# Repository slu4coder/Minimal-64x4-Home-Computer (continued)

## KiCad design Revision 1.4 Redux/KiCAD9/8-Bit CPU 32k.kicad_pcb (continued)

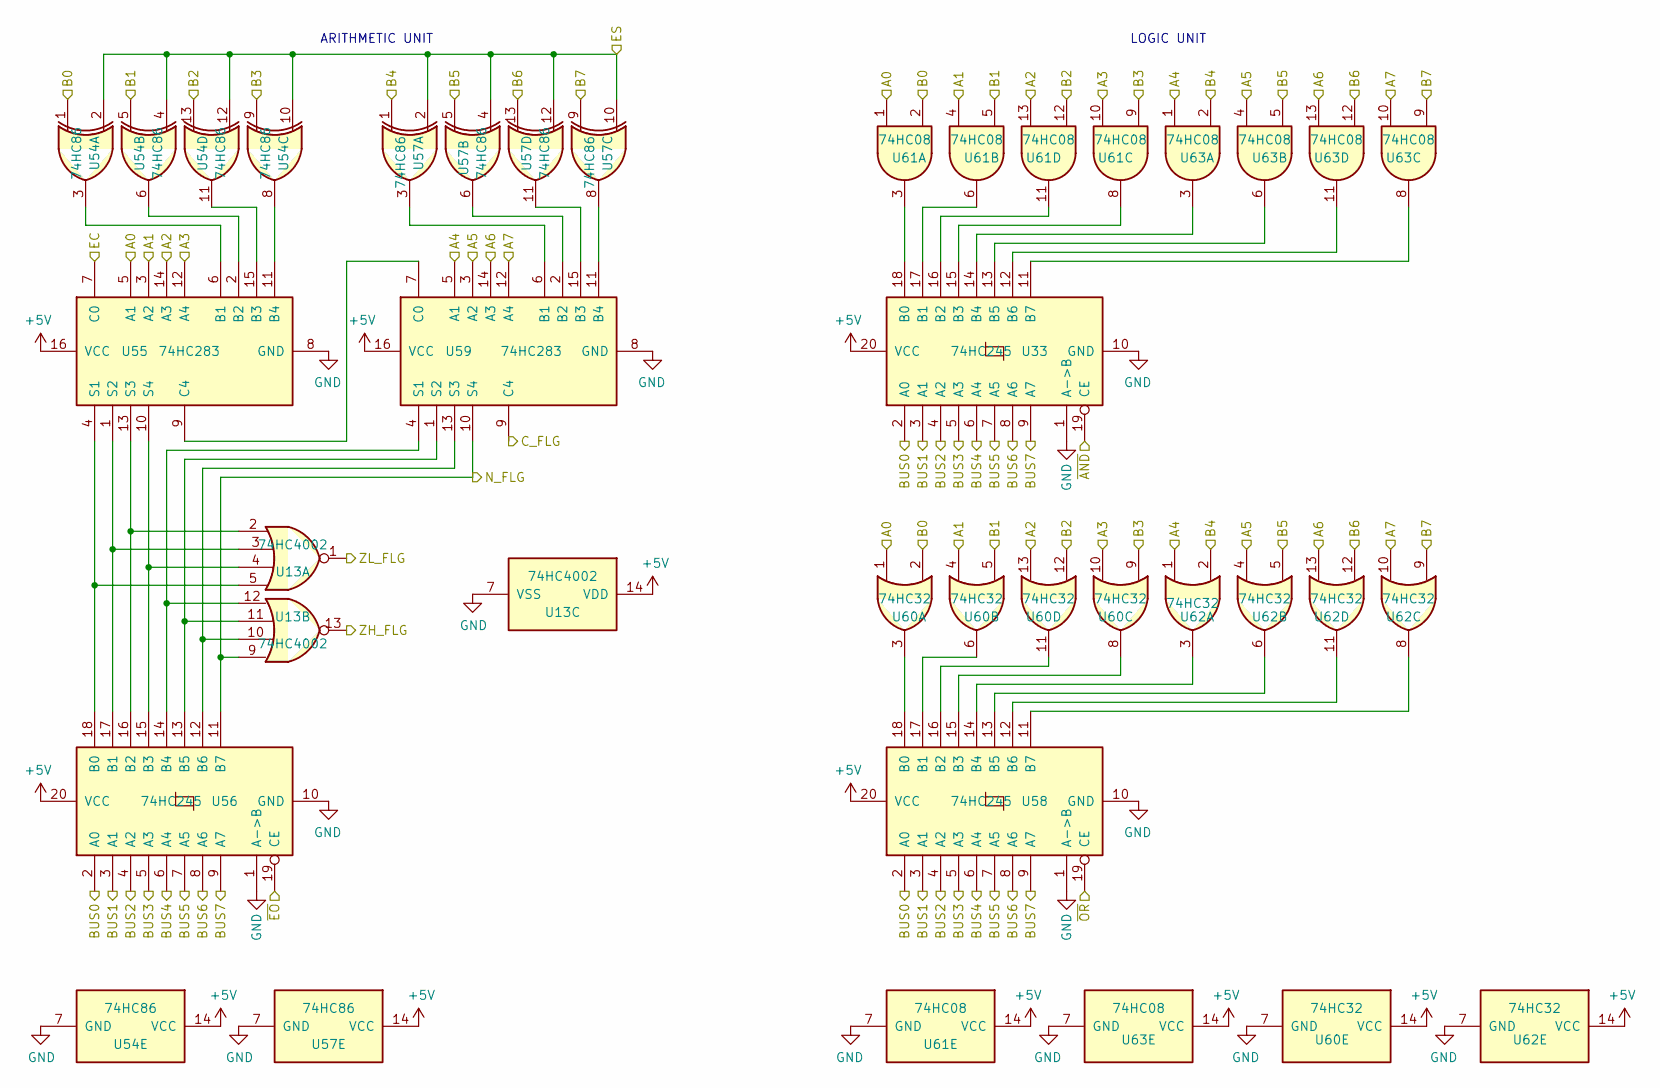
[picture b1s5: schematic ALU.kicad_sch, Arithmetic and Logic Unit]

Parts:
U13: 74HC4002; DIP-14_W7.62mm_Socket
U33, U56, U58: 74HC245; DIP-20_W7.62mm_Socket
U54, U57: 74HC86; DIP-14_W7.62mm_Socket
U55, U59: 74HC283; DIP-16_W7.62mm_Socket
U60, U62: 74HC32; DIP-14_W7.62mm_Socket
U61, U63: 74HC08; DIP-14_W7.62mm_Socket

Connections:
+5V: U13.14 (VDD), U33.20 (VCC), U54.14 (VCC), U55.16 (VCC), U56.20 (VCC), U57.14 (VCC), U58.20 (VCC), U59.16 (VCC), U60.14 (VCC), U61.14 (VCC), U62.14 (VCC), U63.14 (VCC); also elsewhere on the board
/ALU/A0: U55.5 (A1), U60.1, U61.1; also elsewhere on the board
/ALU/A1: U55.3 (A2), U60.4, U61.4; also elsewhere on the board
/ALU/A2: U55.14 (A3), U60.13, U61.13; also elsewhere on the board
/ALU/A3: U55.12 (A4), U60.10, U61.10; also elsewhere on the board
/ALU/A4: U59.5 (A1), U62.1, U63.1; also elsewhere on the board
/ALU/A5: U59.3 (A2), U62.4, U63.4; also elsewhere on the board
/ALU/A6: U59.14 (A3), U62.13, U63.13; also elsewhere on the board
/ALU/A7: U59.12 (A4), U62.10, U63.10; also elsewhere on the board
/ALU/B0: U54.1, U60.2, U61.2; also elsewhere on the board
/ALU/B1: U54.5, U60.5, U61.5; also elsewhere on the board
/ALU/B2: U54.13, U60.12, U61.12; also elsewhere on the board
/ALU/B3: U54.9, U60.9, U61.9; also elsewhere on the board
/ALU/B4: U57.1, U62.2, U63.2; also elsewhere on the board
/ALU/B5: U57.5, U62.5, U63.5; also elsewhere on the board
/ALU/B6: U57.13, U62.12, U63.12; also elsewhere on the board
/ALU/B7: U57.9, U62.9, U63.9; also elsewhere on the board
/ALU/BUS0: U33.2 (A0), U56.2 (A0), U58.2 (A0); also elsewhere on the board
/ALU/BUS1: U33.3 (A1), U56.3 (A1), U58.3 (A1); also elsewhere on the board
/ALU/BUS2: U33.4 (A2), U56.4 (A2), U58.4 (A2); also elsewhere on the board
/ALU/BUS3: U33.5 (A3), U56.5 (A3), U58.5 (A3); also elsewhere on the board
/ALU/BUS4: U33.6 (A4), U56.6 (A4), U58.6 (A4); also elsewhere on the board
/ALU/BUS5: U33.7 (A5), U56.7 (A5), U58.7 (A5); also elsewhere on the board
/ALU/BUS6: U33.8 (A6), U56.8 (A6), U58.8 (A6); also elsewhere on the board
/ALU/BUS7: U33.9 (A7), U56.9 (A7), U58.9 (A7); also elsewhere on the board
/ALU/C_FLG: U59.9 (C4); also elsewhere on the board
/ALU/EC: U55.7 (C0); also elsewhere on the board
/ALU/ES: U54.2, U54.4, U54.10, U54.12, U57.2, U57.4, U57.10, U57.12; also elsewhere on the board
/ALU/N_FLG: U13.9, U56.11 (B7), U59.10 (S4); also elsewhere on the board
/ALU/ZH_FLG: U13.13; also elsewhere on the board
/ALU/ZL_FLG: U13.1; also elsewhere on the board
/ALU/~AND: U33.19 (CE); also elsewhere on the board
/ALU/~EO: U56.19 (CE); also elsewhere on the board
/ALU/~OR: U58.19 (CE); also elsewhere on the board
GND: U13.7 (VSS), U33.1 (A->B), U33.10 (GND), U54.7 (GND), U55.8 (GND), U56.1 (A->B), U56.10 (GND), U57.7 (GND), U58.1 (A->B), U58.10 (GND), U59.8 (GND), U60.7 (GND), U61.7 (GND), U62.7 (GND), U63.7 (GND); also elsewhere on the board
unnamed: U33.18 (B0), U61.3
unnamed: U33.17 (B1), U61.6
unnamed: U33.16 (B2), U61.11
unnamed: U33.15 (B3), U61.8
unnamed: U33.14 (B4), U63.3
unnamed: U33.13 (B5), U63.6
unnamed: U33.12 (B6), U63.11
unnamed: U33.11 (B7), U63.8
unnamed: U54.3, U55.6 (B1)
unnamed: U54.6, U55.2 (B2)
unnamed: U54.11, U55.15 (B3)
unnamed: U54.8, U55.11 (B4)
unnamed: U55.9 (C4), U59.7 (C0)
unnamed: U13.5, U55.4 (S1), U56.18 (B0)
unnamed: U13.3, U55.1 (S2), U56.17 (B1)
unnamed: U13.2, U55.13 (S3), U56.16 (B2)
unnamed: U13.4, U55.10 (S4), U56.15 (B3)
unnamed: U13.12, U56.14 (B4), U59.4 (S1)
unnamed: U13.11, U56.13 (B5), U59.1 (S2)
unnamed: U13.10, U56.12 (B6), U59.13 (S3)
unnamed: U58.18 (B0), U60.3
unnamed: U58.17 (B1), U60.6
unnamed: U58.16 (B2), U60.11
unnamed: U58.15 (B3), U60.8
unnamed: U58.14 (B4), U62.3
unnamed: U58.13 (B5), U62.6
unnamed: U58.12 (B6), U62.11
unnamed: U58.11 (B7), U62.8
unnamed: U57.3, U59.6 (B1)
unnamed: U57.6, U59.2 (B2)
unnamed: U57.11, U59.15 (B3)
unnamed: U57.8, U59.11 (B4)

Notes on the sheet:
ARITHMETIC UNIT
LOGIC UNIT

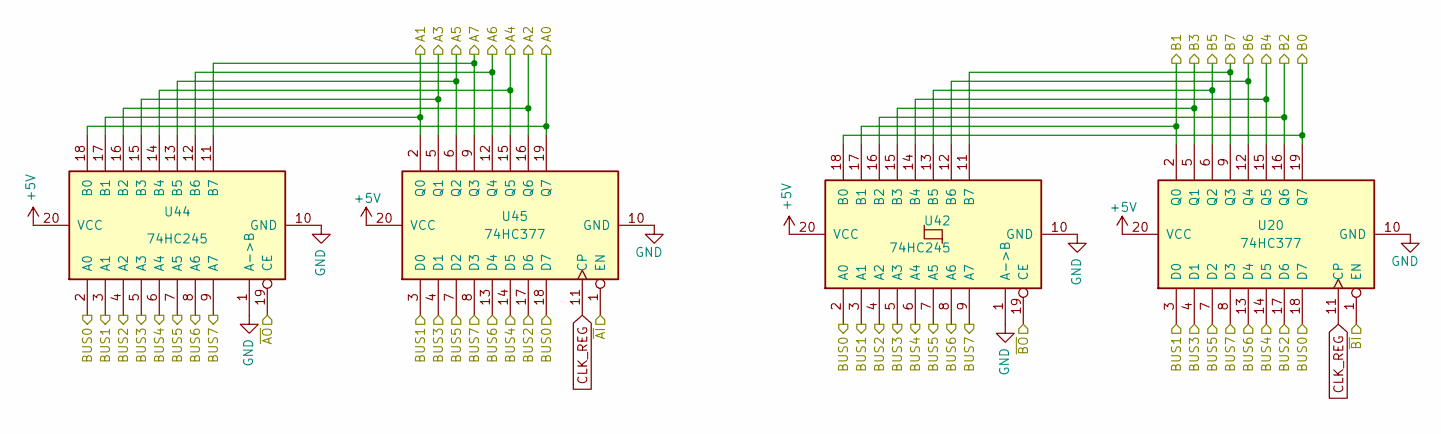
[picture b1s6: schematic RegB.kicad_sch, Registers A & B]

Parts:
U20, U45: 74HC377; DIP-20_W7.62mm_Socket
U42, U44: 74HC245; DIP-20_W7.62mm_Socket

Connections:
+5V: U20.20 (VCC), U42.20 (VCC), U44.20 (VCC), U45.20 (VCC); also elsewhere on the board
/ALU/A0: U44.18 (B0), U45.19 (Q7); also elsewhere on the board
/ALU/A1: U44.17 (B1), U45.2 (Q0); also elsewhere on the board
/ALU/A2: U44.16 (B2), U45.16 (Q6); also elsewhere on the board
/ALU/A3: U44.15 (B3), U45.5 (Q1); also elsewhere on the board
/ALU/A4: U44.14 (B4), U45.15 (Q5); also elsewhere on the board
/ALU/A5: U44.13 (B5), U45.6 (Q2); also elsewhere on the board
/ALU/A6: U44.12 (B6), U45.12 (Q4); also elsewhere on the board
/ALU/A7: U44.11 (B7), U45.9 (Q3); also elsewhere on the board
/ALU/B0: U20.19 (Q7), U42.18 (B0); also elsewhere on the board
/ALU/B1: U20.2 (Q0), U42.17 (B1); also elsewhere on the board
/ALU/B2: U20.16 (Q6), U42.16 (B2); also elsewhere on the board
/ALU/B3: U20.5 (Q1), U42.15 (B3); also elsewhere on the board
/ALU/B4: U20.15 (Q5), U42.14 (B4); also elsewhere on the board
/ALU/B5: U20.6 (Q2), U42.13 (B5); also elsewhere on the board
/ALU/B6: U20.12 (Q4), U42.12 (B6); also elsewhere on the board
/ALU/B7: U20.9 (Q3), U42.11 (B7); also elsewhere on the board
/ALU/BUS0: U20.18 (D7), U42.2 (A0), U44.2 (A0), U45.18 (D7); also elsewhere on the board
/ALU/BUS1: U20.3 (D0), U42.3 (A1), U44.3 (A1), U45.3 (D0); also elsewhere on the board
/ALU/BUS2: U20.17 (D6), U42.4 (A2), U44.4 (A2), U45.17 (D6); also elsewhere on the board
/ALU/BUS3: U20.4 (D1), U42.5 (A3), U44.5 (A3), U45.4 (D1); also elsewhere on the board
/ALU/BUS4: U20.14 (D5), U42.6 (A4), U44.6 (A4), U45.14 (D5); also elsewhere on the board
/ALU/BUS5: U20.7 (D2), U42.7 (A5), U44.7 (A5), U45.7 (D2); also elsewhere on the board
/ALU/BUS6: U20.13 (D4), U42.8 (A6), U44.8 (A6), U45.13 (D4); also elsewhere on the board
/ALU/BUS7: U20.8 (D3), U42.9 (A7), U44.9 (A7), U45.8 (D3); also elsewhere on the board
/Control Logic/~AI: U45.1 (EN); also elsewhere on the board
/Control Logic/~AO: U44.19 (CE); also elsewhere on the board
/Control Logic/~BI: U20.1 (EN); also elsewhere on the board
/Control Logic/~BO: U42.19 (CE); also elsewhere on the board
CLK_REG: U20.11 (CP), U45.11 (CP); also elsewhere on the board
GND: U20.10 (GND), U42.1 (A->B), U42.10 (GND), U44.1 (A->B), U44.10 (GND), U45.10 (GND); also elsewhere on the board

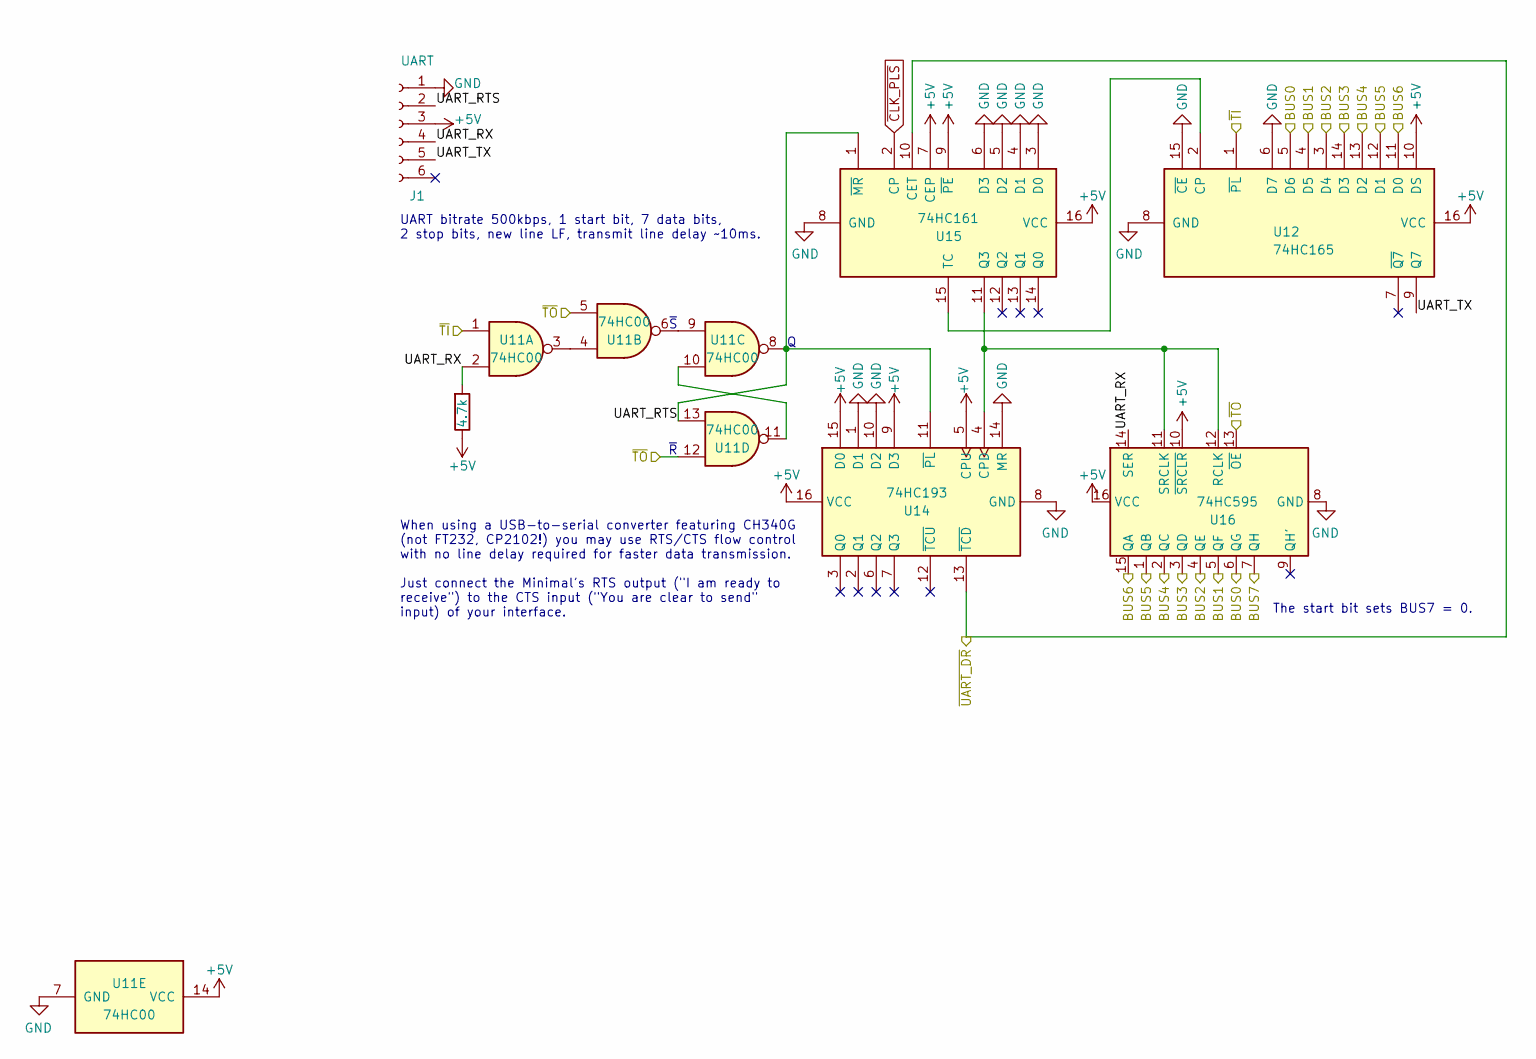
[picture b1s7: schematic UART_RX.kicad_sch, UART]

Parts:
J1: UART; PinSocket_1x06_P2.54mm_Vertical
R1: 4.7k; R_Axial_DIN0207_L6.3mm_D2.5mm_P7.62mm_Horizontal
U11: 74HC00; DIP-14_W7.62mm_Socket
U12: 74HC165; DIP-16_W7.62mm_Socket
U14: 74HC193; DIP-16_W7.62mm_Socket
U15: 74HC161; DIP-16_W7.62mm_Socket
U16: 74HC595; DIP-16_W7.62mm_Socket

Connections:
+5V: J1.3, R1.1, U11.14 (VCC), U12.10 (DS), U12.16 (VCC), U14.5 (CPU), U14.9 (D3), U14.15 (D0), U14.16 (VCC), U15.7 (CEP), U15.9 (~PE), U15.16 (VCC), U16.10 (~SRCLR), U16.16 (VCC); also elsewhere on the board
/ALU/BUS0: U12.5 (D6), U16.6 (QG); also elsewhere on the board
/ALU/BUS1: U12.4 (D5), U16.5 (QF); also elsewhere on the board
/ALU/BUS2: U12.3 (D4), U16.4 (QE); also elsewhere on the board
/ALU/BUS3: U12.14 (D3), U16.3 (QD); also elsewhere on the board
/ALU/BUS4: U12.13 (D2), U16.2 (QC); also elsewhere on the board
/ALU/BUS5: U12.12 (D1), U16.1 (QB); also elsewhere on the board
/ALU/BUS6: U12.11 (D0), U16.15 (QA); also elsewhere on the board
/ALU/BUS7: U16.7 (QH); also elsewhere on the board
/Control Logic/~TI: U11.1, U12.1 (~PL); also elsewhere on the board
/Control Logic/~TO: U11.5, U11.12, U16.13 (~OE); also elsewhere on the board
/Control Logic/~UART_DR: U14.13 (~TCD), U15.10 (CET); also elsewhere on the board
/UART/UART_RTS: J1.2, U11.8, U11.13, U14.11 (~PL), U15.1 (~MR)
/UART/UART_RX: J1.4, R1.2, U11.2, U16.14 (SER)
/UART/UART_TX: J1.5, U12.9 (Q7)
GND: J1.1, U11.7 (GND), U12.6 (D7), U12.8 (GND), U12.15 (~CE), U14.1 (D1), U14.8 (GND), U14.10 (D2), U14.14 (MR), U15.3 (D0), U15.4 (D1), U15.5 (D2), U15.6 (D3), U15.8 (GND), U16.8 (GND); also elsewhere on the board
unnamed: U11.3, U11.4
unnamed: U11.6, U11.9
unnamed: U11.10, U11.11
unnamed: U12.2 (CP), U15.15 (TC)
unnamed: U14.4 (CPD), U15.11 (Q3), U16.11 (SRCLK), U16.12 (RCLK)
~CLK_PLS: U15.2 (CP); also elsewhere on the board

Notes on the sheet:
~{S}
UART bitrate 500kbps, 1 start bit, 7 data bits, 2 stop bits, new line LF, transmit line delay ~10ms.
~{R}
The start bit sets BUS7 = 0.
When using a USB-to-serial converter featuring CH340G (not FT232, CP2102!) you may use RTS/CTS flow control with no line delay required for faster data transmission. Just connect the Minimal's RTS output ("I am ready to receive") to the CTS input ("You are clear to send" input) of your interface.

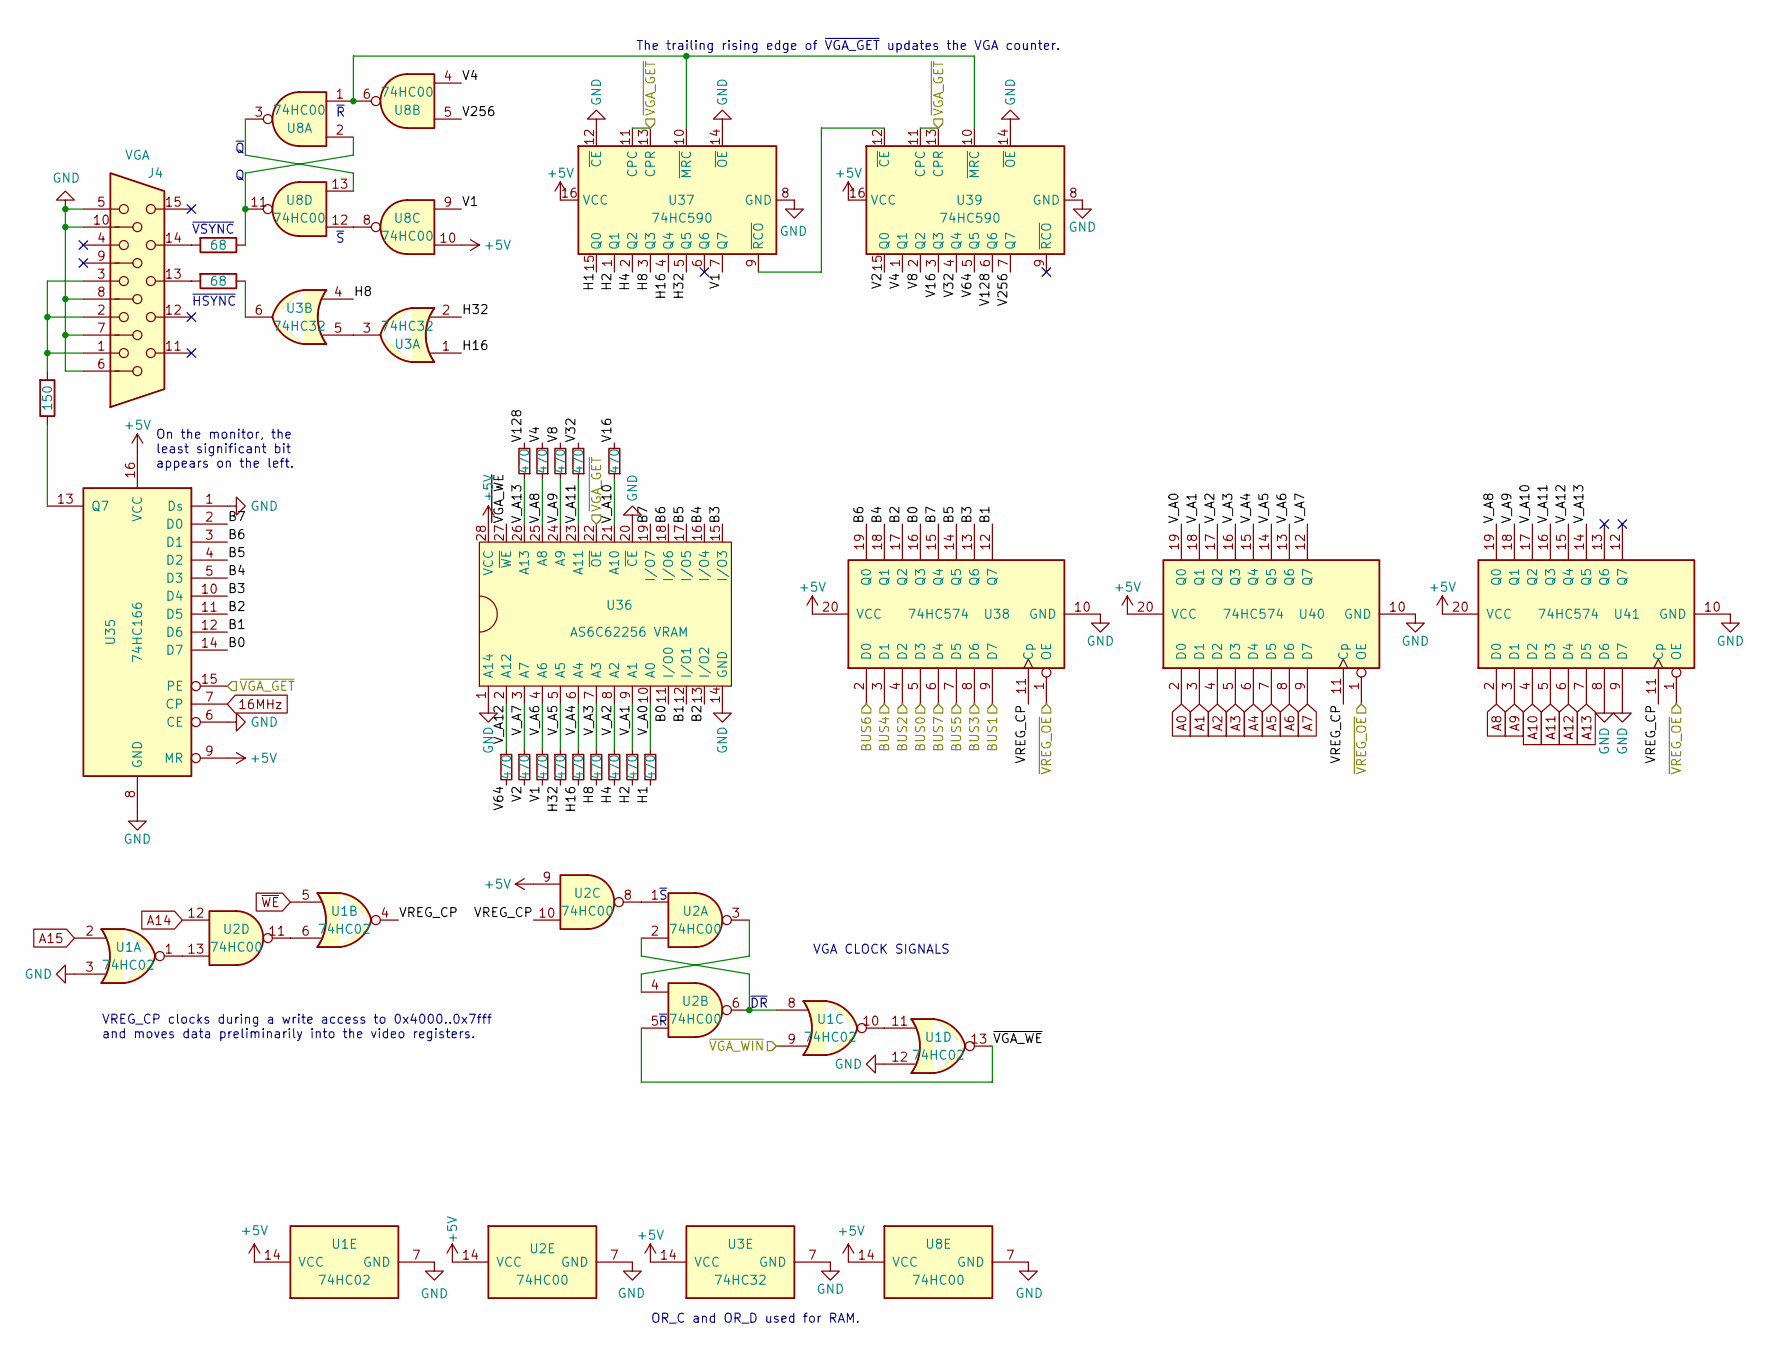
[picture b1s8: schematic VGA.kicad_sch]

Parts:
J4: VGA; VGA DSUB15HD_female
R6: 150; R_Axial_DIN0207_L6.3mm_D2.5mm_P7.62mm_Horizontal
R7, R8: 68; R_Axial_DIN0207_L6.3mm_D2.5mm_P7.62mm_Horizontal
R9, R10, R11, R12, R13, R14, R15, R16, R17, R18, R19, R20, R21, R22: 470; R_Axial_DIN0207_L6.3mm_D2.5mm_P7.62mm_Horizontal
U1: 74HC02; DIP-14_W7.62mm_Socket
U2, U8: 74HC00; DIP-14_W7.62mm_Socket
U3: 74HC32; DIP-14_W7.62mm_Socket
U35: 74HC166; DIP-16_W7.62mm_Socket
U36: AS6C62256 VRAM; DIP-28_W15.24mm_Socket
U37, U39: 74HC590; DIP-16_W7.62mm_Socket
U38, U40, U41: 74HC574; DIP-20_W7.62mm_Socket

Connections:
16MHz: U35.7 (CP); also elsewhere on the board
+5V: U1.14 (VCC), U2.9, U2.14 (VCC), U3.14 (VCC), U8.10, U8.14 (VCC), U35.9 (MR), U35.16 (VCC), U36.28 (VCC), U37.16 (VCC), U38.20 (VCC), U39.16 (VCC), U40.20 (VCC), U41.20 (VCC); also elsewhere on the board
/ALU/BUS0: U38.5 (D3); also elsewhere on the board
/ALU/BUS1: U38.9 (D7); also elsewhere on the board
/ALU/BUS2: U38.4 (D2); also elsewhere on the board
/ALU/BUS3: U38.8 (D6); also elsewhere on the board
/ALU/BUS4: U38.3 (D1); also elsewhere on the board
/ALU/BUS5: U38.7 (D5); also elsewhere on the board
/ALU/BUS6: U38.2 (D0); also elsewhere on the board
/ALU/BUS7: U38.6 (D4); also elsewhere on the board
/Control Logic/~VGA_GET: U35.15 (PE), U36.22 (~OE), U37.11 (CPC), U37.13 (CPR), U39.11 (CPC), U39.13 (CPR); also elsewhere on the board
/Control Logic/~VGA_TRY: U1.9; also elsewhere on the board
/Control Logic/~VREG_OE: U38.1 (OE), U40.1 (OE), U41.1 (OE); also elsewhere on the board
/VGA/B0: U35.14 (D7), U36.11 (I/O0), U38.16 (Q3)
/VGA/B1: U35.12 (D6), U36.12 (I/O1), U38.12 (Q7)
/VGA/B2: U35.11 (D5), U36.13 (I/O2), U38.17 (Q2)
/VGA/B3: U35.10 (D4), U36.15 (I/O3), U38.13 (Q6)
/VGA/B4: U35.5 (D3), U36.16 (I/O4), U38.18 (Q1)
/VGA/B5: U35.4 (D2), U36.17 (I/O5), U38.14 (Q5)
/VGA/B6: U35.3 (D1), U36.18 (I/O6), U38.19 (Q0)
/VGA/B7: U35.2 (D0), U36.19 (I/O7), U38.15 (Q4)
/VGA/H1: R9.2, U37.15 (Q0)
/VGA/H2: R10.2, U37.1 (Q1)
/VGA/H4: R11.2, U37.2 (Q2)
/VGA/H8: R12.2, U3.4, U37.3 (Q3)
/VGA/H16: R13.2, U3.1, U37.4 (Q4)
/VGA/H32: R14.2, U3.2, U37.5 (Q5)
/VGA/V1: R15.2, U8.9, U37.7 (Q7)
/VGA/V2: R16.2, U39.15 (Q0)
/VGA/V4: R17.2, U8.4, U39.1 (Q1)
/VGA/V8: R18.2, U39.2 (Q2)
/VGA/V16: R19.2, U39.3 (Q3)
/VGA/V32: R20.2, U39.4 (Q4)
/VGA/V64: R21.2, U39.5 (Q5)
/VGA/V128: R22.2, U39.6 (Q6)
/VGA/V256: U8.5, U39.7 (Q7)
/VGA/VREG_CP: U1.4, U2.10, U38.11 (Cp), U40.11 (Cp), U41.11 (Cp)
/VGA/V_A0: R9.1, U36.10 (A0), U40.19 (Q0)
/VGA/V_A1: R10.1, U36.9 (A1), U40.18 (Q1)
/VGA/V_A2: R11.1, U36.8 (A2), U40.17 (Q2)
/VGA/V_A3: R12.1, U36.7 (A3), U40.16 (Q3)
/VGA/V_A4: R13.1, U36.6 (A4), U40.15 (Q4)
/VGA/V_A5: R14.1, U36.5 (A5), U40.14 (Q5)
/VGA/V_A6: R15.1, U36.4 (A6), U40.13 (Q6)
/VGA/V_A7: R16.1, U36.3 (A7), U40.12 (Q7)
/VGA/V_A8: R17.1, U36.25 (A8), U41.19 (Q0)
/VGA/V_A9: R18.1, U36.24 (A9), U41.18 (Q1)
/VGA/V_A10: R19.1, U36.21 (A10), U41.17 (Q2)
/VGA/V_A11: R20.1, U36.23 (A11), U41.16 (Q3)
/VGA/V_A12: R21.1, U36.2 (A12), U41.15 (Q4)
/VGA/V_A13: R22.1, U36.26 (A13), U41.14 (Q5)
/VGA/~VGA_WE: U1.13, U2.5, U36.27 (~WE)
A0: U40.2 (D0); also elsewhere on the board
A1: U40.3 (D1); also elsewhere on the board
A2: U40.4 (D2); also elsewhere on the board
A3: U40.5 (D3); also elsewhere on the board
A4: U40.6 (D4); also elsewhere on the board
A5: U40.7 (D5); also elsewhere on the board
A6: U40.8 (D6); also elsewhere on the board
A7: U40.9 (D7); also elsewhere on the board
A8: U41.2 (D0); also elsewhere on the board
A9: U41.3 (D1); also elsewhere on the board
A10: U41.4 (D2); also elsewhere on the board
A11: U41.5 (D3); also elsewhere on the board
A12: U41.6 (D4); also elsewhere on the board
A13: U41.7 (D5); also elsewhere on the board
A14: U2.12; also elsewhere on the board
A15: U1.2; also elsewhere on the board
GND: J4.5, J4.6, J4.7, J4.8, J4.10, U1.3, U1.7 (GND), U1.12, U2.7 (GND), U3.7 (GND), U8.7 (GND), U35.1 (Ds), U35.6 (CE), U35.8 (GND), U36.1 (A14), U36.14 (GND), U36.20 (~CE), U37.8 (GND), U37.12 (~CE), U37.14 (~OE), U38.10 (GND), U39.8 (GND), U39.14 (~OE), U40.10 (GND), U41.8 (D6), U41.9 (D7), U41.10 (GND); also elsewhere on the board
unnamed: J4.1, J4.2, J4.3, R6.2
unnamed: J4.13, R8.2
unnamed: J4.14, R7.2
unnamed: R7.1, U8.2, U8.11
unnamed: R8.1, U3.6
unnamed: U1.1, U2.13
unnamed: U1.6, U2.11
unnamed: U1.8, U2.2, U2.6
unnamed: U1.10, U1.11
unnamed: U2.1, U2.8
unnamed: U2.3, U2.4
unnamed: U3.3, U3.5
unnamed: U8.8, U8.12
unnamed: U8.3, U8.13
unnamed: R6.1, U35.13 (Q7)
unnamed: U8.1, U8.6, U37.10 (~MRC), U39.10 (~MRC)
unnamed: U37.9 (~RCO), U39.12 (~CE)
~WE: U1.5; also elsewhere on the board

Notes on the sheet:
~{S}
VREG_CP clocks during a write access to 0x4000..0x7fff and moves data preliminarily into the video registers.
~{DR}
~{R}
On the monitor, the least significant bit appears on the left.
~{Q}
~{HSYNC}
OR_C and OR_D used for RAM.
~{VSYNC}
The trailing rising edge of ~{VGA_GET} updates the VGA counter.
VGA CLOCK SIGNALS

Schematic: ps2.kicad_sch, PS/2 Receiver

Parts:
J2: PS/2; FP_MINI_DIN_6_PS2
R3, R4: 4.7k; R_Axial_DIN0207_L6.3mm_D2.5mm_P7.62mm_Horizontal
U9: 74HCT132; DIP-14_W7.62mm_Socket
U17: 74HC595; DIP-16_W7.62mm_Socket
U18: 74HC193; DIP-16_W7.62mm_Socket

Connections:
+5V: J2.4, R3.1, R4.1, U9.9, U9.14 (VCC), U17.10 (~SRCLR), U17.16 (VCC), U18.1 (D1), U18.5 (CPU), U18.9 (D3), U18.16 (VCC); also elsewhere on the board
/ALU/BUS0: U17.7 (QH); also elsewhere on the board
/ALU/BUS1: U17.6 (QG); also elsewhere on the board
/ALU/BUS2: U17.5 (QF); also elsewhere on the board
/ALU/BUS3: U17.4 (QE); also elsewhere on the board
/ALU/BUS4: U17.3 (QD); also elsewhere on the board
/ALU/BUS5: U17.2 (QC); also elsewhere on the board
/ALU/BUS6: U17.1 (QB); also elsewhere on the board
/ALU/BUS7: U17.15 (QA); also elsewhere on the board
/Control Logic/~KO: U9.5, U17.13 (~OE); also elsewhere on the board
/Control Logic/~PS2_DR: U9.12, U18.13 (~TCD); also elsewhere on the board
/PS2 Receiver/PS2_CLK: J2.5, R3.2, U9.13
/PS2 Receiver/PS2_DAT: J2.1, R4.2, U9.1, U17.14 (SER)
GND: J2.3, U9.7 (GND), U17.8 (GND), U18.8 (GND), U18.10 (D2), U18.14 (MR), U18.15 (D0); also elsewhere on the board
unnamed: U9.2, U9.6
unnamed: U9.10, U9.11
unnamed: U17.12 (RCLK), U18.3 (Q0)
unnamed: U9.8, U17.11 (SRCLK), U18.4 (CPD)
unnamed: U9.3, U9.4, U18.11 (~PL)

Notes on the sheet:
(green)
(yellow)
~{Q}
The order of the bits is intentionally reversed.
~{TCD} goes LOW at the falling edge of CPD after reaching zero at the beginning of the high stop bit ensuring that a full transmission has been sampled. Note that RCLK is driven by Q0 which happens *after* CPD. Thus RCLK always samples the *current*, not the previous register state. RCLK is driven 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
For PS/2 devices with only 3.3V output use 74HCT132 for maximum robustness.
~{R}
~{S}
74HCxx input rise time (10-90%) is required to be <400ns. Use 74HC132 (NAND with Schmitt trigger inputs) rather than 74HC00 here, since PS/2 signals can have rise and fall times >400ns.

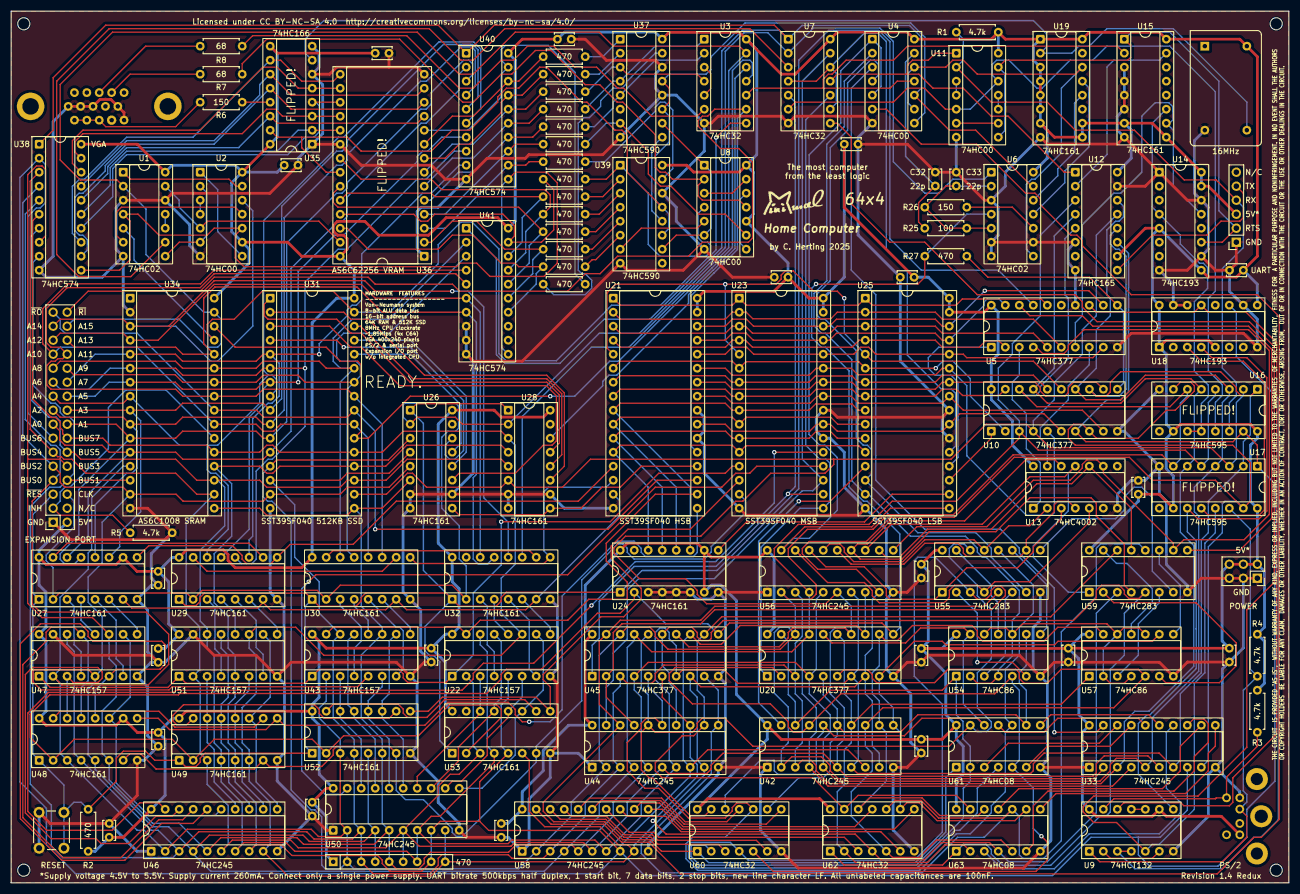
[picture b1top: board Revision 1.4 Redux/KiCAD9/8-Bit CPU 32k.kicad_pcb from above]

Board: 2 copper layers, 231.8 x 158.1 mm, 122 parts (0 on the bottom side), 263 nets.
